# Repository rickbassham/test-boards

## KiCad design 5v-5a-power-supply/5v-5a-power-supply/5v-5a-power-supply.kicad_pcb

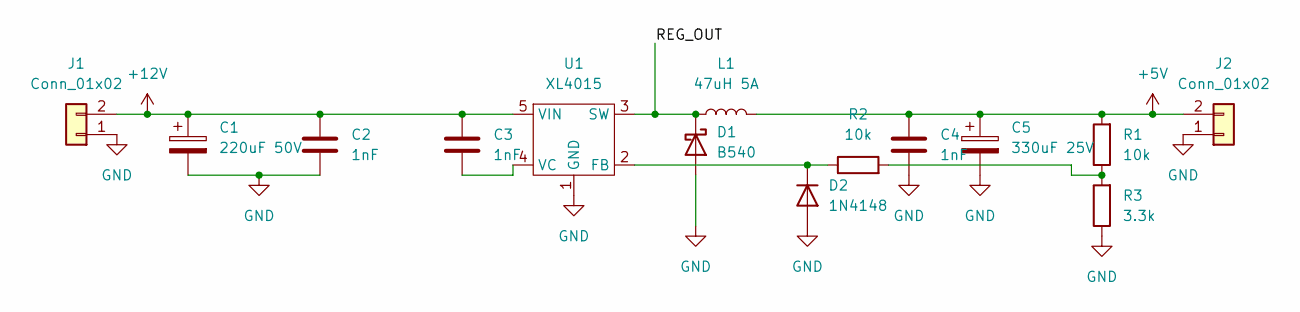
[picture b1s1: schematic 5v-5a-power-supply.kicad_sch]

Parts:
C1: 220uF 50V; CP_Elec_10x10.5
C2, C3, C4: 1nF; C_0402_1005Metric
C5: 330uF 25V; CP_Elec_10x10.5
D1: B540; D_SMC; LCSC C72264
D2: 1N4148; D_SOD-523; LCSC C232841
J1, J2: Conn_01x02; PinHeader_1x02_P2.54mm_Vertical
L1: 47uH 5A; L_12x12mm_H6mm
R1, R2: 10k; R_0402_1005Metric
R3: 3.3k; R_0402_1005Metric
U1: XL4015; TO-263-5_TabPin3; LCSC C51661

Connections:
+5V: C4.1, C5.1, J2.2, L1.2, R1.2
+12V: C1.1, C2.1, C3.1, J1.2, U1.5 (VIN)
/REG_OUT: D1.1 (K), L1.1, U1.3 (SW)
GND: C1.2, C2.2, C4.2, C5.2, D1.2 (A), D2.2 (A), J1.1, J2.1, R3.1, U1.1 (GND)
unnamed: C3.2, U1.4 (VC)
unnamed: D2.1 (K), R2.1, U1.2 (FB)
unnamed: R1.1, R2.2, R3.2

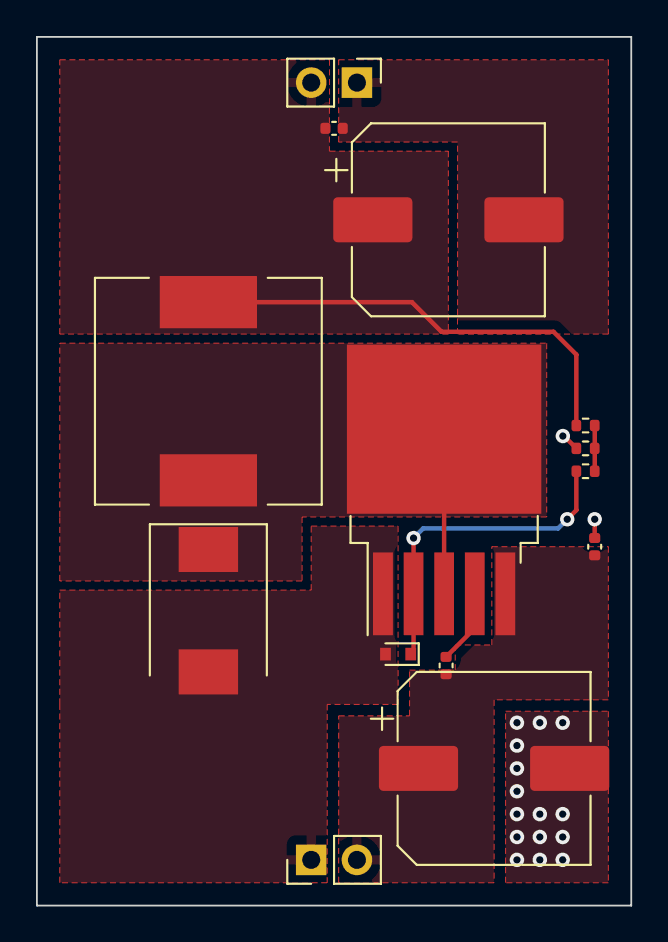
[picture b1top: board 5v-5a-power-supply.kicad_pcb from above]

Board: 2 copper layers, 33.0 x 48.3 mm, 14 parts (0 on the bottom side), 7 nets.

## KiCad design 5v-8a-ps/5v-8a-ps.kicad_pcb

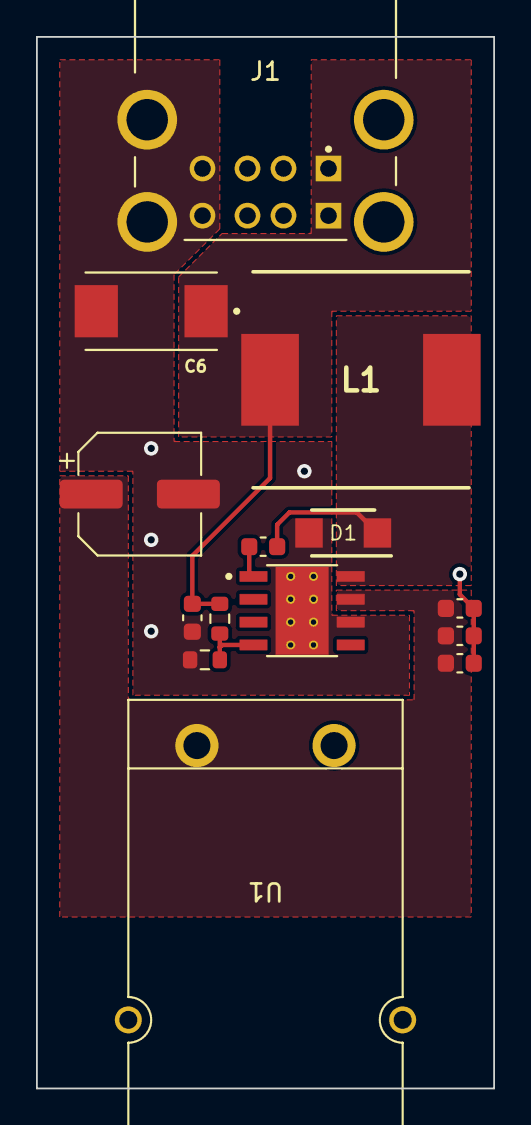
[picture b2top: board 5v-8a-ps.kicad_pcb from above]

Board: 2 copper layers, 25.4 x 58.4 mm, 14 parts (0 on the bottom side), 6 nets.

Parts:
C1: 470uF; CP_Elec_6.3x7.7
C2, C5, C7: 0.01uF; C_0603_1608Metric
C3, C4: 4.7uF; C_0603_1608Metric
C6: 330uF; CAP_6TPB330ML
D1: 40V_5A; SODFL4626X120N
J1: 1903815-1; TE_1903815-1
L1: 15uH; INDPM120120X800N
R1: 10k; R_0603_1608Metric
R2: 3.16k; R_0603_1608Metric
U1: PP25-1317G12-BK
U4: TPS5450DDAR; CONV_TPS5450DDAR

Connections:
+5V: C6.1, C7.1, J1.1 (VBUS2), J1.5 (VBUS1), L1.2, R1.2
+12V: C1.1, C3.1, C4.1, C5.1, U1.1 (RED), U4.7 (VIN)
/PH: C2.2, D1.1 (K), L1.1, U4.8 (PH)
GND: C1.2, C3.2, C4.2, C5.2, C6.2, C7.2, D1.2 (A), J1.4 (GND2), J1.8 (GND1), J1.P1 (SHIELD), J1.P2 (SHIELD), J1.P3 (SHIELD), J1.P4 (SHIELD), R2.1, U1.2 (BLACK), U4.6 (GND), U4.9 (PwPd)
unnamed: C2.1, U4.1 (BOOT)
unnamed: R1.1, R2.2, U4.4 (VSNS)

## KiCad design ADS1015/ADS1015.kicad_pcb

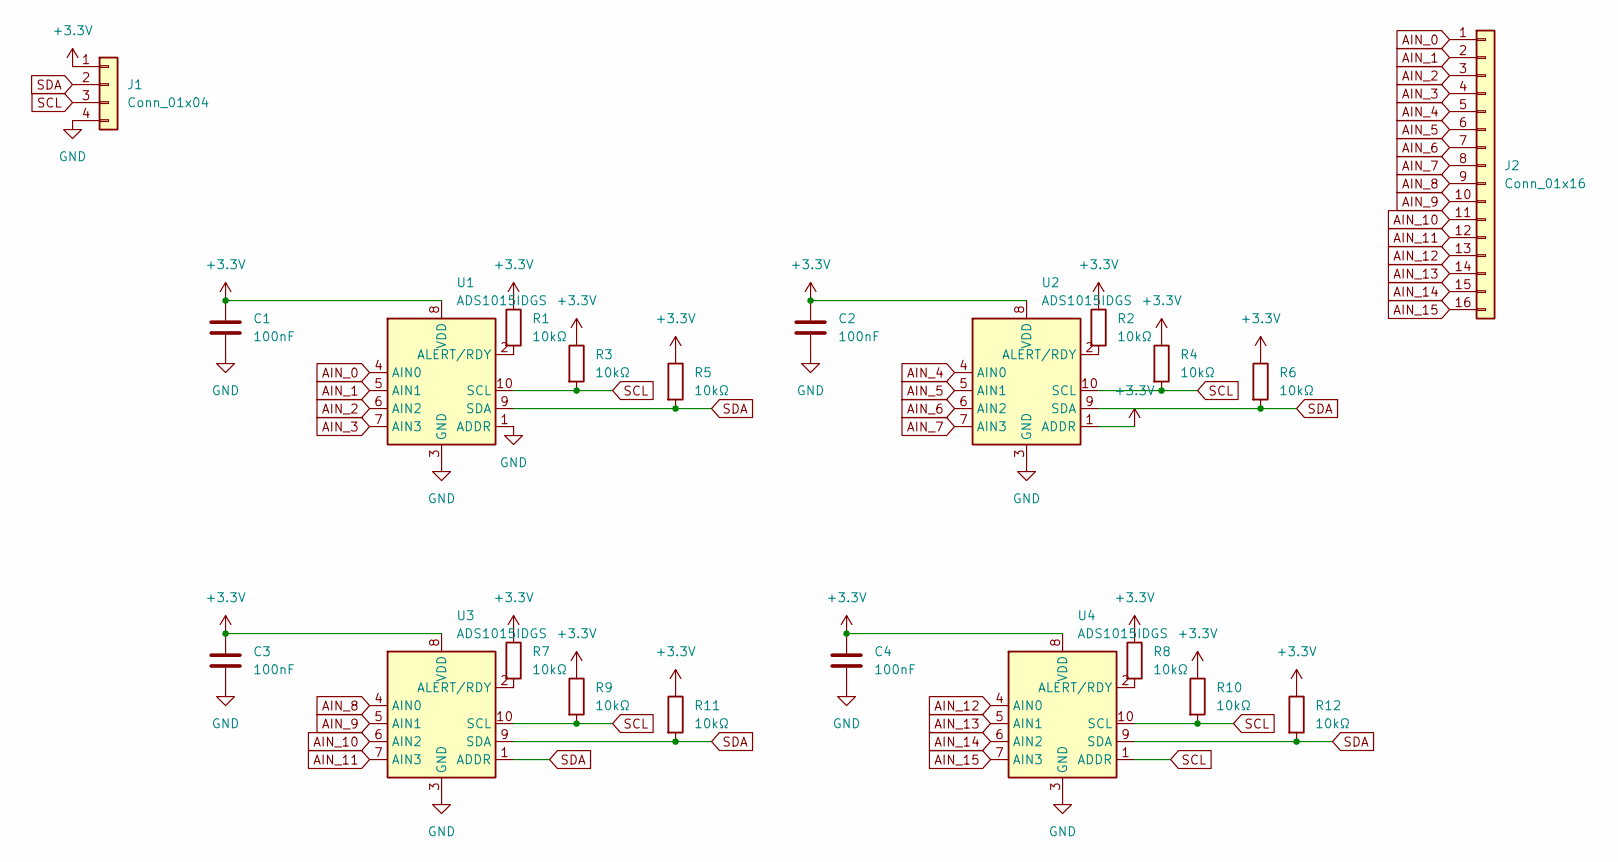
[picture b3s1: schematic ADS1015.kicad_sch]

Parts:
C1, C2, C3, C4: 100nF; C_0402_1005Metric
J1: Conn_01x04; PinHeader_1x04_P2.54mm_Vertical
J2: Conn_01x16; PinHeader_1x16_P2.54mm_Vertical
R1, R2, R3, R4, R5, R6, R7, R8, R9, R10, R11, R12: 10kΩ; R_0402_1005Metric; LCSC C25744
U1, U2, U3, U4: ADS1015IDGS; TSSOP-10_3x3mm_P0.5mm

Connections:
+3V3: C1.1, C2.1, C3.1, C4.1, J1.1, R1.1, R2.1, R3.1, R4.1, R5.1, R6.1, R7.1, R8.1, R9.1, R10.1, R11.1, R12.1, U1.8 (VDD), U2.1 (ADDR), U2.8 (VDD), U3.8 (VDD), U4.8 (VDD)
AIN_0: J2.1, U1.4 (AIN0)
AIN_1: J2.2, U1.5 (AIN1)
AIN_2: J2.3, U1.6 (AIN2)
AIN_3: J2.4, U1.7 (AIN3)
AIN_4: J2.5, U2.4 (AIN0)
AIN_5: J2.6, U2.5 (AIN1)
AIN_6: J2.7, U2.6 (AIN2)
AIN_7: J2.8, U2.7 (AIN3)
AIN_8: J2.9, U3.4 (AIN0)
AIN_9: J2.10, U3.5 (AIN1)
AIN_10: J2.11, U3.6 (AIN2)
AIN_11: J2.12, U3.7 (AIN3)
AIN_12: J2.13, U4.4 (AIN0)
AIN_13: J2.14, U4.5 (AIN1)
AIN_14: J2.15, U4.6 (AIN2)
AIN_15: J2.16, U4.7 (AIN3)
GND: C1.2, C2.2, C3.2, C4.2, J1.4, U1.1 (ADDR), U1.3 (GND), U2.3 (GND), U3.3 (GND), U4.3 (GND)
unnamed: R1.2, U1.2 (ALERT/RDY)
unnamed: R2.2, U2.2 (ALERT/RDY)
unnamed: R7.2, U3.2 (ALERT/RDY)
unnamed: R8.2, U4.2 (ALERT/RDY)
SCL: J1.3, R3.2, R4.2, R9.2, R10.2, U1.10 (SCL), U2.10 (SCL), U3.10 (SCL), U4.1 (ADDR), U4.10 (SCL)
SDA: J1.2, R5.2, R6.2, R11.2, R12.2, U1.9 (SDA), U2.9 (SDA), U3.1 (ADDR), U3.9 (SDA), U4.9 (SDA)

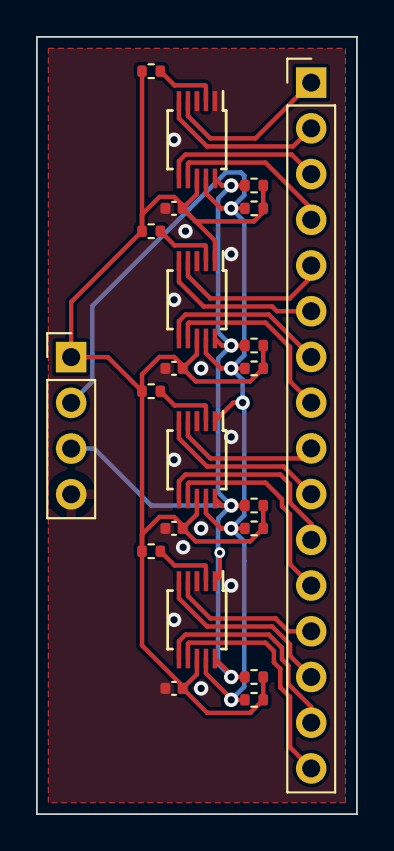
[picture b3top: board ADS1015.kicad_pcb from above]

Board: 2 copper layers, 17.8 x 43.2 mm, 22 parts (0 on the bottom side), 24 nets.

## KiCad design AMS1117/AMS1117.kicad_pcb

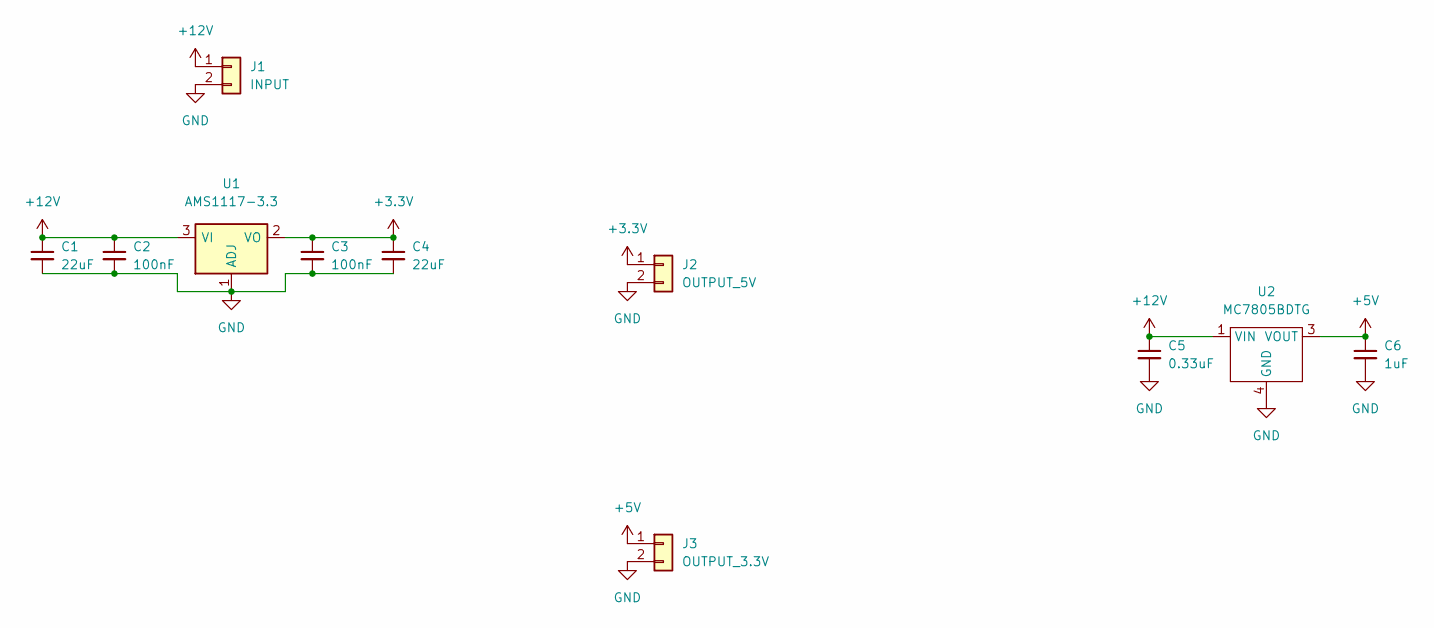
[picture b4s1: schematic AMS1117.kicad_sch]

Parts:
C1, C4: 22uF; C_0805_2012Metric; LCSC C45783
C2, C3: 100nF; C_0402_1005Metric; LCSC C307331
C5: 0.33uF; C_0805_2012Metric
C6: 1uF; C_0805_2012Metric
J1: INPUT; PinHeader_1x02_P2.54mm_Vertical
J2: OUTPUT_5V; PinHeader_1x02_P2.54mm_Vertical
J3: OUTPUT_3.3V; PinHeader_1x02_P2.54mm_Vertical
U1: AMS1117-3.3; SOT-223-3_TabPin2; LCSC C6186
U2: MC7805BDTG; TO229P990X238-4N; LCSC C83632

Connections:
+3V3: C3.1, C4.1, J2.1, U1.2 (VO)
+5V: C6.1, J3.1, U2.3 (VOUT)
+12V: C1.1, C2.1, C5.1, J1.1, U1.3 (VI), U2.1 (VIN)
GND: C1.2, C2.2, C3.2, C4.2, C5.2, C6.2, J1.2, J2.2, J3.2, U1.1 (ADJ), U2.4 (GND)

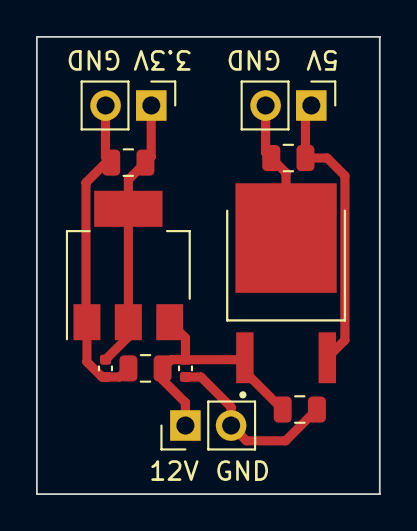
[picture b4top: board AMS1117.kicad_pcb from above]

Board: 2 copper layers, 19.1 x 25.4 mm, 11 parts (0 on the bottom side), 4 nets.

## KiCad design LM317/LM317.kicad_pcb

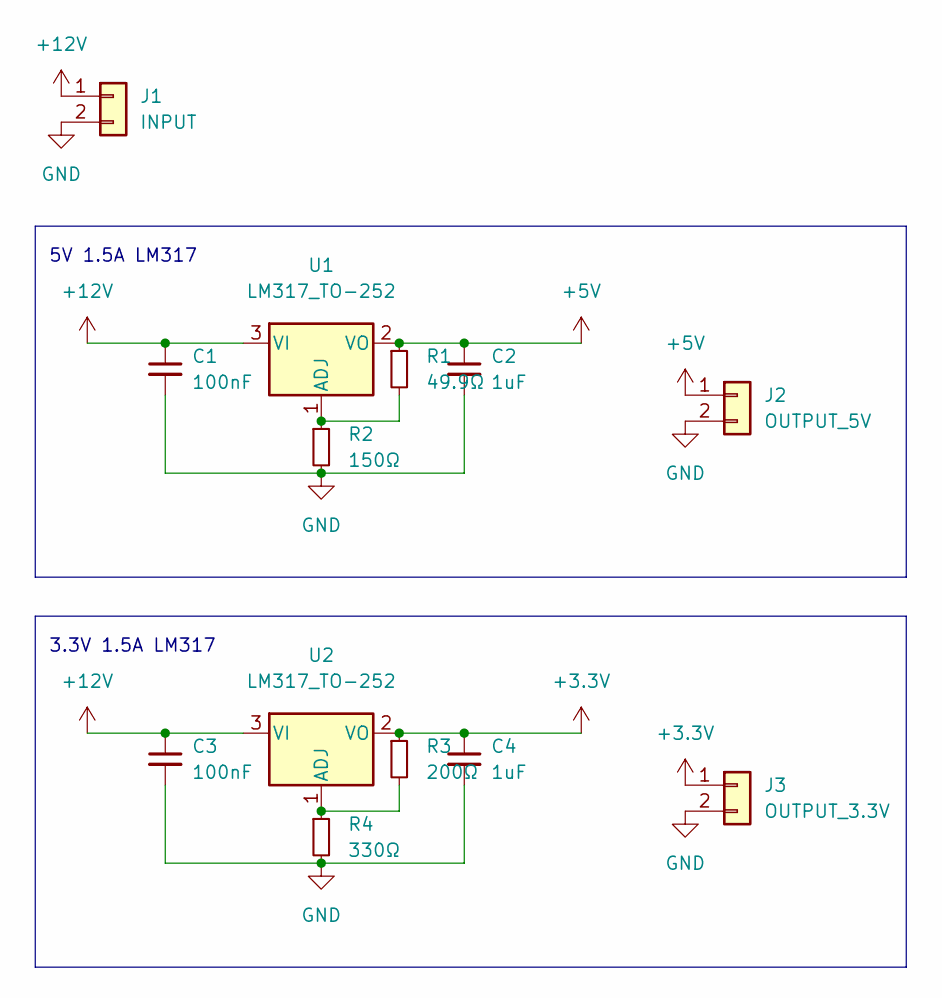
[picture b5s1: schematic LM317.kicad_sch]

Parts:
C1, C3: 100nF; C_0402_1005Metric; LCSC C307331
C2, C4: 1uF; C_0402_1005Metric; LCSC C52923
J1: INPUT; PinHeader_1x02_P2.54mm_Vertical
J2: OUTPUT_5V; PinHeader_1x02_P2.54mm_Vertical
J3: OUTPUT_3.3V; PinHeader_1x02_P2.54mm_Vertical
R1: 49.9Ω; R_0402_1005Metric; LCSC C25120
R2: 150Ω; R_0402_1005Metric; LCSC C25082
R3: 200Ω; R_0402_1005Metric; LCSC C25087
R4: 330Ω; R_0402_1005Metric; LCSC C25104
U1, U2: LM317_TO-252; TO-252-2; LCSC C75510

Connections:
+3V3: C4.1, J3.1, R3.1, U2.2 (VO)
+5V: C2.1, J2.1, R1.1, U1.2 (VO)
+12V: C1.1, C3.1, J1.1, U1.3 (VI), U2.3 (VI)
GND: C1.2, C2.2, C3.2, C4.2, J1.2, J2.2, J3.2, R2.2, R4.2
unnamed: R1.2, R2.1, U1.1 (ADJ)
unnamed: R3.2, R4.1, U2.1 (ADJ)

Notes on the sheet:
5V 1.5A LM317
3.3V 1.5A LM317

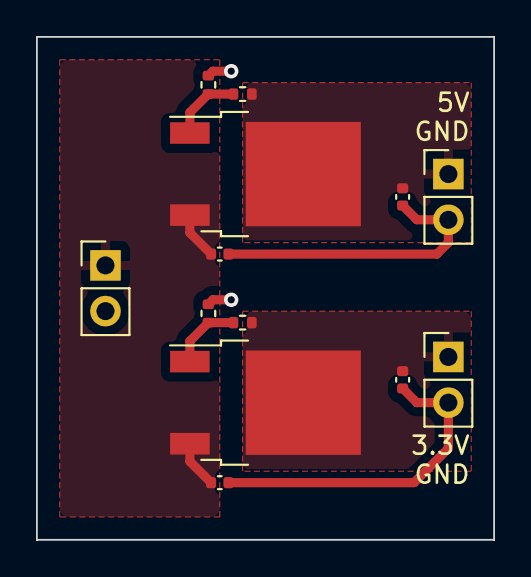
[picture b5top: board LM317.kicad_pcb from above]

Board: 2 copper layers, 25.4 x 27.9 mm, 13 parts (0 on the bottom side), 6 nets.

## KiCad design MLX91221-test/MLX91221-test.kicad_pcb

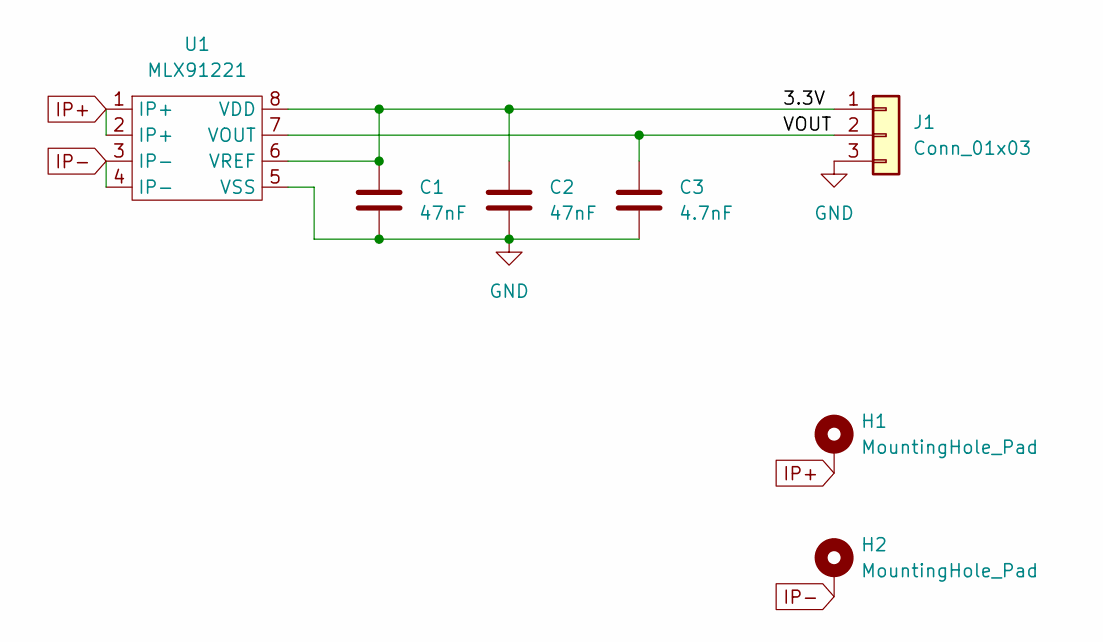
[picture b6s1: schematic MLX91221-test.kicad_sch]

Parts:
C1, C2: 47nF; C_0603_1608Metric; LCSC C1622
C3: 4.7nF; C_0603_1608Metric; LCSC C53987
H1, H2: MountingHole_Pad; MountingHole_3.2mm_M3_DIN965_Pad
J1: Conn_01x03; PinHeader_1x03_P2.54mm_Vertical
U1: MLX91221; SOIC-8_3.9x4.9mm_P1.27mm

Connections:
/3.3V: C1.1, C2.1, J1.1, U1.6 (VREF), U1.8 (VDD)
/VOUT: C3.1, J1.2, U1.7 (VOUT)
GND: C1.2, C2.2, C3.2, J1.3, U1.5 (VSS)
IP+: H1.1, U1.1 (IP+), U1.2 (IP+)
IP-: H2.1, U1.3 (IP-), U1.4 (IP-)

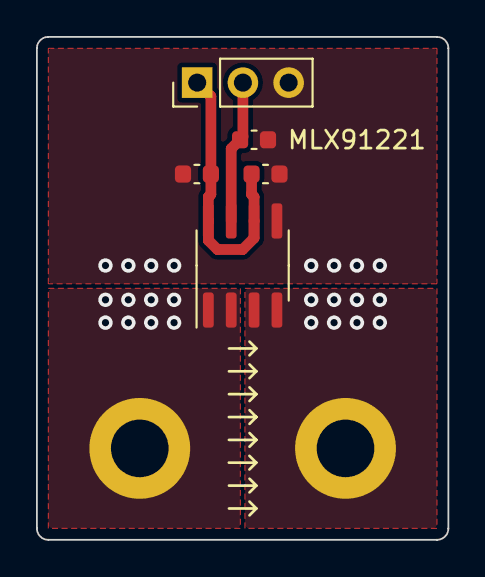
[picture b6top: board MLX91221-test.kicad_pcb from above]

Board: 2 copper layers, 22.9 x 27.9 mm, 7 parts (0 on the bottom side), 5 nets.

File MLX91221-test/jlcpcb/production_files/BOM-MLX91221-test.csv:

Comment,Designator,Footprint,LCSC
47nF,"C1,C2",C_0603_1608Metric,C1622
4.7nF,C3,C_0603_1608Metric,C53987
MLX91221,U1,SOIC-8_3.9x4.9mm_P1.27mm,

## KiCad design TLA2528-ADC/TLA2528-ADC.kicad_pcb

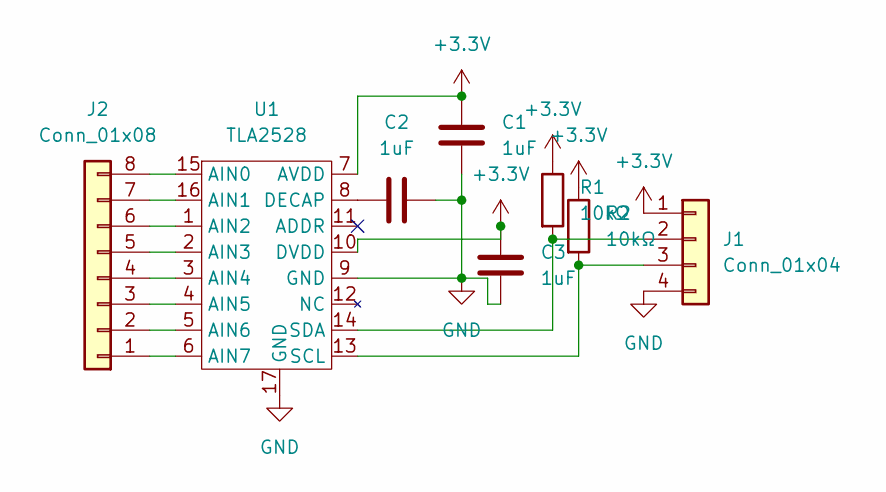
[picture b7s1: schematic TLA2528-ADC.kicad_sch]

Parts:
C1, C2, C3: 1uF; C_0603_1608Metric
J1: Conn_01x04; PinHeader_1x04_P2.54mm_Vertical
J2: Conn_01x08; PinHeader_1x08_P2.54mm_Vertical
R1, R2: 10kΩ; R_0402_1005Metric; LCSC C25744
U1: TLA2528; WQFN-16-1EP_3x3mm_P0.5mm_EP1.6x1.6mm

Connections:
+3V3: C1.1, C3.1, J1.1, R1.1, R2.1, U1.7 (AVDD), U1.10 (DVDD)
GND: C1.2, C2.2, C3.2, J1.4, U1.9 (GND), U1.17 (GND)
unnamed: C2.1, U1.8 (DECAP)
unnamed: J1.2, R1.2, U1.14 (SDA)
unnamed: J1.3, R2.2, U1.13 (SCL)
unnamed: J2.1, U1.6 (AIN7)
unnamed: J2.2, U1.5 (AIN6)
unnamed: J2.3, U1.4 (AIN5)
unnamed: J2.4, U1.3 (AIN4)
unnamed: J2.5, U1.2 (AIN3)
unnamed: J2.6, U1.1 (AIN2)
unnamed: J2.7, U1.16 (AIN1)
unnamed: J2.8, U1.15 (AIN0)

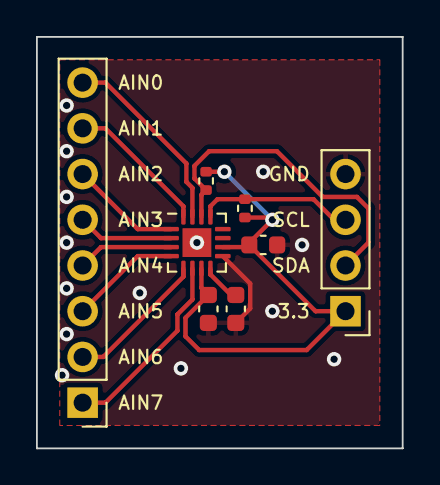
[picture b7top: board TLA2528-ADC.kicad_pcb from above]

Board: 2 copper layers, 20.3 x 22.9 mm, 8 parts (0 on the bottom side), 13 nets.

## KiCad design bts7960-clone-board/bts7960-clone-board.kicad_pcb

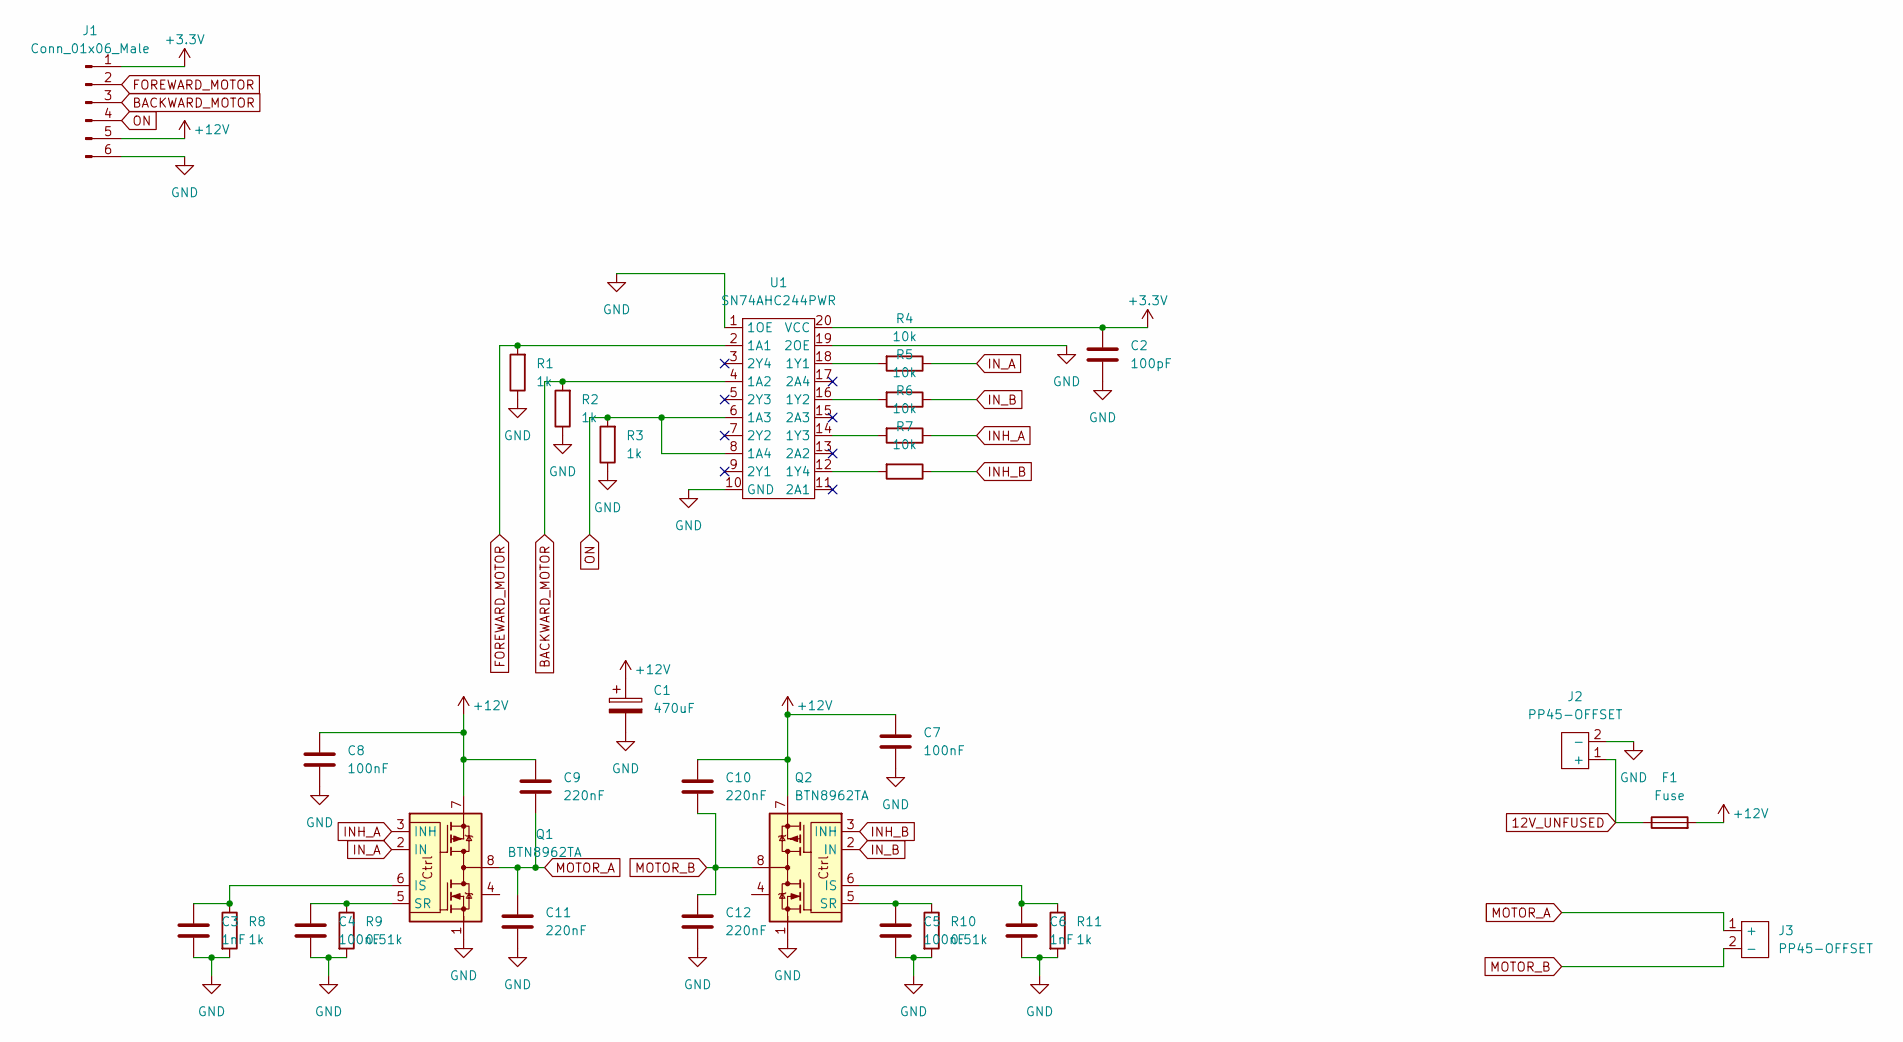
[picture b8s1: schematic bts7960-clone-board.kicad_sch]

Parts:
C1: 470uF; CP_Radial_D8.0mm_P3.50mm; Manufacturer Part 860020474014; DigiKey Part 732-8831-1-ND
C2: 100pF; C_0603_1608Metric; jlc 0603
C3, C6: 1nF; C_0603_1608Metric; jlc 0603
C4, C5, C7, C8: 100nF; C_0603_1608Metric; jlc 0603
C9, C10, C11, C12: 220nF; C_0603_1608Metric; jlc 0603
F1: Fuse; Keystone 3522-2 Fuse Holder; Manufacturer Part 3522-2; DigiKey Part 36-3522-2-ND
J1: Conn_01x06_Male; PinHeader_1x06_P2.54mm_Vertical
J2, J3: PP45-OFFSET; PP45-SHORT; Manufacturer Part 1336G1; DigiKey Part 2243-1336G1-ND
Q1, Q2: BTN8962TA; TO-263-7_TabPin8; jlc TO-263-7
R1, R2, R3, R8, R11: 1k; R_0603_1608Metric; jlc 0603
R4, R5, R6, R7: 10k; R_0603_1608Metric; jlc 0603
R9, R10: 0.51k; R_0603_1608Metric; jlc 0603
U1: SN74AHC244PWR; TSSOP-20_4.4x6.5mm_P0.65mm; jlc TSSOP20_44MM_065P

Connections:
12V_UNFUSED: F1.1, J2.1 (+)
+3.3V: C2.1, J1.1, U1.20 (VCC)
+12V: C1.1, C7.1, C8.1, C9.1, C10.1, F1.2, J1.5, Q1.7, Q2.7
BACKWARD_MOTOR: J1.3, R2.2, U1.4 (1A2)
FOREWARD_MOTOR: J1.2, R1.2, U1.2 (1A1)
GND: C1.2, C2.2, C3.2, C4.2, C5.2, C6.2, C7.2, C8.2, C11.2, C12.2, J1.6, J2.2 (-), Q1.1, Q2.1, R1.1, R2.1, R3.1, R8.2, R9.2, R10.2, R11.2, U1.1 (1OE), U1.10 (GND), U1.19 (2OE)
INH_A: Q1.3 (INH), R6.1
INH_B: Q2.3 (INH), R7.1
IN_A: Q1.2 (IN), R4.1
IN_B: Q2.2 (IN), R5.1
MOTOR_A: C9.2, C11.1, J3.1 (+), Q1.4, Q1.8
MOTOR_B: C10.2, C12.1, J3.2 (-), Q2.4, Q2.8
unnamed: C3.1, Q1.6 (IS), R8.1
unnamed: C4.1, Q1.5 (SR), R9.1
unnamed: C5.1, Q2.5 (SR), R10.1
unnamed: C6.1, Q2.6 (IS), R11.1
unnamed: R4.2, U1.18 (1Y1)
unnamed: R5.2, U1.16 (1Y2)
unnamed: R6.2, U1.14 (1Y3)
unnamed: R7.2, U1.12 (1Y4)
ON: J1.4, R3.2, U1.6 (1A3), U1.8 (1A4)

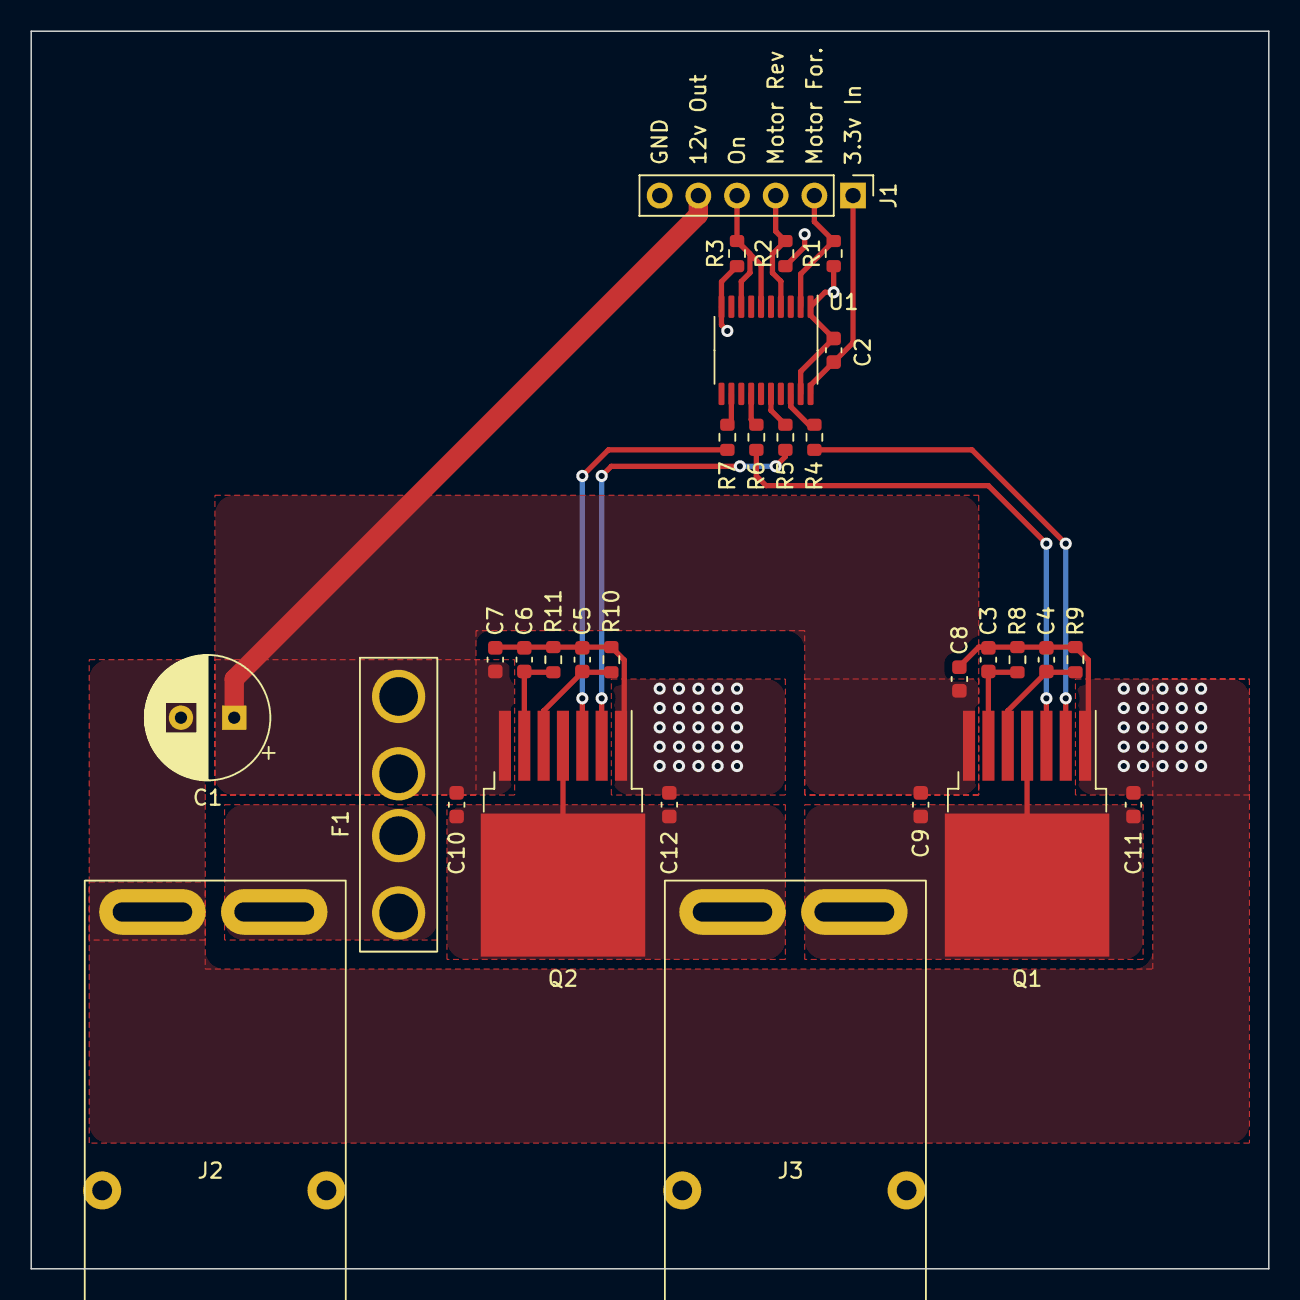
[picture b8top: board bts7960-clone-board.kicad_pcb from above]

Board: 2 copper layers, 81.3 x 81.3 mm, 30 parts (0 on the bottom side), 21 nets.
